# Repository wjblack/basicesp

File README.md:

BasicESP Hardware
=================

Introduction
------------

This repository houses the PCB design for the BasicESP project.  The
[ESP8266](https://en.wikipedia.org/wiki/ESP8266) is a super-cheap chip that
has:

   * 802.11n WiFi
   * An 80 MHz Tensilica Xtensa microcontroller
   * 64+96k of I+D RAM
   * An SDIO interface
   * And a bunch of GPIO, PWM, and other SoCish goodness

It can be used either as a SDIO-attached device or as a standalone
microcontroller and is available for about $2 via
[AliExpress](http://aliexpress.com) on a module such as the
[ESP-12F](http://www.esp8266.com/viewtopic.php?f=5&t=5520), which is what this
PCB design assumes.  Assuming an ESP-12, this board adds:

   * 2mm pads for the ESP wifi module (the board has overhang/clearance space
     for the module so that the antenna gets no interference from the board).
     This makes it very easy to mount the ESP to the board via 2mm header pins.
   * Built-in 5V->3.3V regulator.
   * A programming switch (to easily put the ESP into programming mode on boot).
   * A serial header (to easily attach an
     [FTDI cable](https://www.sparkfun.com/products/9718)).
   * All the various resistors needed for mode setting and whatnot.

Revisions
---------

[Revison 1](rev1/) was the first pass and was produced in a small batch at
[PCBWay](http://pcbway.com) in January 2017.  It lacked some filter capacitors
that caused issues with some sensors and had various other shortcomings (see
the docs inside for details).

[Revision 2](rev2/) is being produced now at PCBWay.  It includes filter caps
on the power regulator, mounting holes, a power cutoff jumper, and more pins
broken out.

Thanks
------

Many thanks to Niklas Wennerstrand for his excellent series of [intro videos
for kicad on Youtube](https://www.youtube.com/watch?v=uT1QnBSRLHs).  His notes
on producing the output for the manufacturer were particularly useful.

Copying
-------

(C) 2016-17 by [BJ Black](mailto:bj@wjblack.com)

This design is released under the [WTFPL](http://www.wtfpl.net/about/) license
and escapes unto an unsuspecting planet with NO WARRANTY WHATSOEVER, expressed
or implied.  Have fun, ya filthy animals ;-)

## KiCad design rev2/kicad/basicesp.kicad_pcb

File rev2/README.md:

BasicESP Hardware Revision 2.0
==============================

Introduction
------------

This PCB design is the second in the basicesp line.  The basicesp is designed
to use the ESP-12 module and has:

   * 2mm pads for the ESP wifi module (the board has overhang/clearance space
     for the module so that the antenna gets no interference from the board)
   * Built-in 5V->3.3V regulator
   * A programming switch
   * A serial header
   * All the various resistors needed for mode setting

A GPIO header on the left side has the following pinout (from the top):

   1. ADC
   2. GPIO5 (NodeMCU IO Index 1)
   3. GPIO4 (Index 2)
   4. GPIO16 (Index 0)
   5. GPIO14 (Index 5)
   6. GPIO12 (Index 6)
   7. GPIO13 (Index 7)
   8. +5V
   9. GND
   10. +3.3V

Notably an I2C display (like the Sainsmart LCD2004 controller) can be wired
straight to pins 3-6 without any gymnastics.  A typical PIR motion sensor
module can be wired to pins 4-6 with minimal gymnastics (swapping the OUT and
either VCC or GND connection to match ends).

Production and Files
--------------------

This board was sent to manufacture on 6 Feb 2017.

The design was done using kicad for both schematic, netlist, and PCB layout.
The kicad source files are all in [kicad/](kicad/).

When assembled, the board should look like this:

And here is a [PDF of the schematic](schematic.pdf).

Shortcomings
------------

Revision A had two disconnected nodes (notably the +5V through the power header
and a filled region break for ground).  That's been fixed in rev 2.0b.

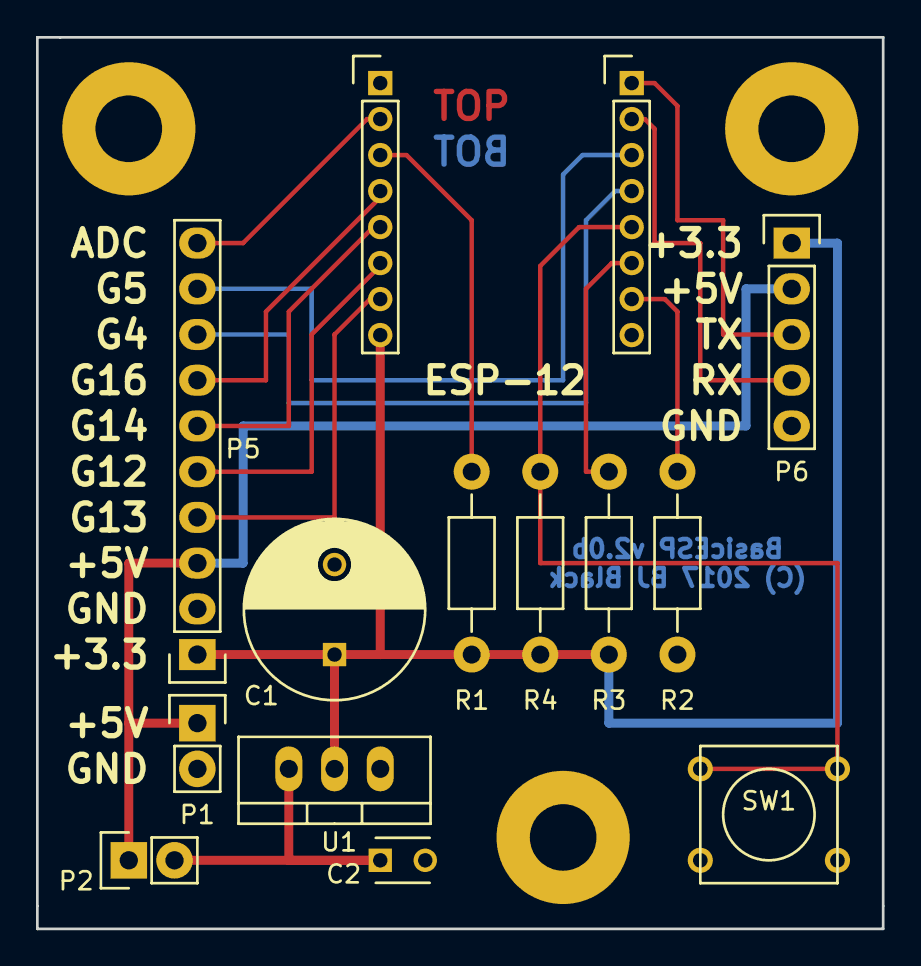
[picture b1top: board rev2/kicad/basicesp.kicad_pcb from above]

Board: 2 copper layers, 47.0 x 49.5 mm, 14 parts (0 on the bottom side), 17 nets.

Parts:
C1: 10u; C_Radial_D10_L16_P5
C2: 100n; C_Disc_D3_P2.5
P1, P2: CONN_01X02; Pin_Header_Straight_1x02
P3, P4: CONN_01X08; Pin_Header_Straight_1x08_Pitch2.00mm
P5: CONN_01X10; Pin_Header_Straight_1x10
P6: CONN_01X05; Pin_Header_Straight_1x05
R1, R2, R3, R4: 4.7k; Resistor_Horizontal_RM10mm
SW1: SW_PUSH_SMALL_H; SW_PUSH_SMALL
U1: LM1117-3.3; TO-220_Neutral123_Vertical

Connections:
+3V3: C1.1, P3.8, P5.1, P6.1, R1.1, R3.2, R4.2, U1.2
+5V: P1.1, P2.1, P5.3, P6.2
/G4: P4.4, P5.8
/G5: P4.3, P5.9
GND: C1.2, C2.2, P1.2, P4.8, P5.2, P6.5, R2.2, SW1.2, U1.1
unnamed: C2.1, P2.2, U1.3
unnamed: P3.2, P5.10
unnamed: P3.3, R1.2
unnamed: P3.4, P5.7
unnamed: P3.5, P5.6
unnamed: P3.6, P5.5
unnamed: P3.7, P5.4
unnamed: P4.1, P6.3
unnamed: P4.2, P6.4
unnamed: P4.5, R4.1, SW1.1
unnamed: P4.6, R3.1
unnamed: P4.7, R2.1

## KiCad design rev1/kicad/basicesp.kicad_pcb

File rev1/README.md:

BasicESP Hardware Revision 1.0
==============================

Introduction
------------

This PCB design was the first manufactured in the basicesp line.  The basicesp
is designed to use the ESP-12 module and has:

   * 2mm pads for the ESP wifi module (the board has overhang/clearance space
     for the module so that the antenna gets no interference from the board)
   * Built-in 5V->3.3V regulator
   * A programming switch
   * A serial header
   * All the various resistors needed for mode setting

A GPIO header on the left side has the following pinout (from the top):

   1. GPIO16 (NodeMCU IO Index 0)
   2. GPIO14 (Index 5)
   3. GPIO12 (Index 6)
   4. GPIO13 (Index 7)
   5. +5V
   6. GND
   7. +3.3V

Notably an I2C display (like the Sainsmart LCD2004 controller) can be wired
straight to pins 3-6 without any gymnastics.  A typical PIR motion sensor
module can be wired to pins 4-6 with minimal gymnastics (swapping the OUT and
either VCC or GND connection to match ends).

Production and Files
--------------------

This board was produced in a 10-unit proto batch at pcbway in Jan, 2017.  The
file bundle I sent to them is in basicesp.wjblack.com.rev.1.0b.zip.

The design was done using kicad for both schematic, netlist, and PCB layout.
The kicad source files are all in [kicad/](kicad/).

When assembled, the board looks like this:

And here is a [PDF of the schematic](schematic.pdf).

Ease of Use
-----------

Developing with this board isn't too bad (indeed, it's much easier to solder up than the 16 individual wires I had to wire for other projects involving the
PIA 2mm pitch).

The parts are surprisingly not too heat-sensitive--I was able to get away with
a fine tip soldering iron and light solder direct on all joints (there are a
lot of plain header connects, which are just straightforward through-hole
soldering).

Shortcomings
------------

The biggest problem with this design is that it does not include the
manufacturer-recommended capacitors for the 3.3V regulator.  The ESP module
doesn't seem to care too much, but variations in power wreak havoc with the PIR
module I tried (soldering the caps directly to the regulator pins afterward
worked well to mitigate those problems).  This will be fixed in Rev 2.

Mounting holes will be added in Rev 2.

It would have been nice to put a +5V rail by the serial so it could be powered
(albeit temporarily) by a FTDI cable all on one side (the evils of attempting
this are debatable--you can *kinda* get away with it if the ESP isn't drawing
too much current.  Real EEs' heads will be exploding right about now, though).
A power and/or reset switch would be a nice-to-have, as would breaking out the
two GPIO pins I left NC.

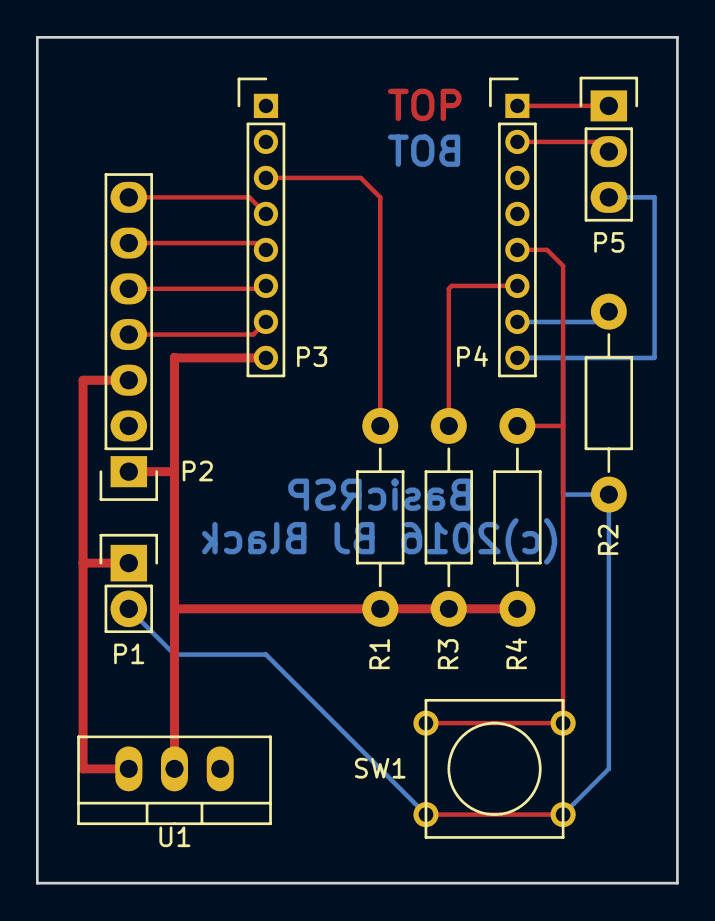
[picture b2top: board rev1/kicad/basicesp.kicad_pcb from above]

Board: 2 copper layers, 35.6 x 47.0 mm, 11 parts (0 on the bottom side), 13 nets.

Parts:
P1: CONN_01X02; Pin_Header_Straight_1x02
P2: CONN_01X07; Pin_Header_Straight_1x07
P3, P4: CONN_01X08; Pin_Header_Straight_1x08_Pitch2.00mm
P5: CONN_01X03; Pin_Header_Straight_1x03
R1, R2, R3, R4: 4.7k; Resistor_Horizontal_RM10mm
SW1: SW_PUSH_SMALL_H; SW_PUSH_SMALL
U1: LM1117-3.3; TO-220_Neutral123_Vertical

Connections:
+3V3: P2.1, P3.8, R1.1, R3.2, R4.2, U1.2
+5V: P1.1, P2.3, U1.3
GND: P1.2, P2.2, P4.8, P5.3, R2.2, SW1.2, U1.1
unnamed: P2.4, P3.7
unnamed: P2.5, P3.6
unnamed: P2.6, P3.5
unnamed: P2.7, P3.4
unnamed: P3.3, R1.2
unnamed: P4.1, P5.1
unnamed: P4.2, P5.2
unnamed: P4.5, R4.1, SW1.1
unnamed: P4.6, R3.1
unnamed: P4.7, R2.1

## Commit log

2017-02-01 Initial commit.
2017-02-07 Add production files.
2017-02-07 Update READMEs
2017-02-24 Update to revision B (fix two disconnected nodes).

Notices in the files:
rev1/kicad/basicesp.kicad_pcb:
(c)2016 BJ Black
rev2/kicad/basicesp.kicad_pcb:
(C) 2017 BJ Black
